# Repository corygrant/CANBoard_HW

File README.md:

# CANBoard_HW
CANBoard is a simple CAN enabled IO board, specifically designed to be used in devices like steering wheels/button boxes/panels/etc.

* 8 digital inputs
    * Ground switching
* 5 analog inputs
    * 5V max
* 4 digital outputs
    * Low side switch (open collector)
    * 0.5A max each
* STM32F303K8
* KiCad 7.0.0

# Goals
- Create a low cost device that my friends and I can use in our project cars
- Use components that are easily soldered by hand (hence 0805) and are preferably from my stock of frequently used parts (ex: LD1117S33CTR)
- Share my work with others for reference, inspiration or collaboration. 

If this project does help you in any way, I'd appreciate a message!

# [Store](https://dingo-electronics.square.site/product/canboard/3)

# Disclaimer
Please note that this product has been designed by a hobbyist, not a professional. It is intended for off-road and testing use only. Users should operate the product at their own discretion and risk. The designer explicitly disclaims any responsibility for damage or injury that may result from the use of this product.

# Schematic
[Schematic PDF](/Export/V2/CANBoard_HW_V2.pdf)

# DBC

DBC file can be found [here](https://github.com/corygrant/CANBoard_FW/tree/main/dbc)

# BOM

[Interactive BOM](https://htmlpreview.github.io/?https://github.com/corygrant/CANBoard_HW/blob/main/docs/bom/ibom.html)

# Jumpers
**CAN Term** : Soldering this jumper enables the 120 ohm terminating resistor across CANL/CANH

**CAN ID Jumpers 1 and 2** : Soldering these jumpers allows different base CAN IDs to be selected when using multiple CANBoards in the same bus
| 1      | 2      | Base CAN ID (Hex)|
| ------ | ------ | ----- |
| Open   | Open   | 0x640 |
| Closed | Open   | 0x650 |
| Open   | Closed | 0x660 |
| Closed | Closed | 0x670 |

# Firmware
[CANBoard firmware](https://github.com/corygrant/CANBoard_FW)

# Updating Firmware
Use [Tag Connect TC2030 cable](https://www.tag-connect.com/product/tc2030-ctx-nl-stdc14-for-use-with-stm32-processors-with-stlink-v3) 

# Images

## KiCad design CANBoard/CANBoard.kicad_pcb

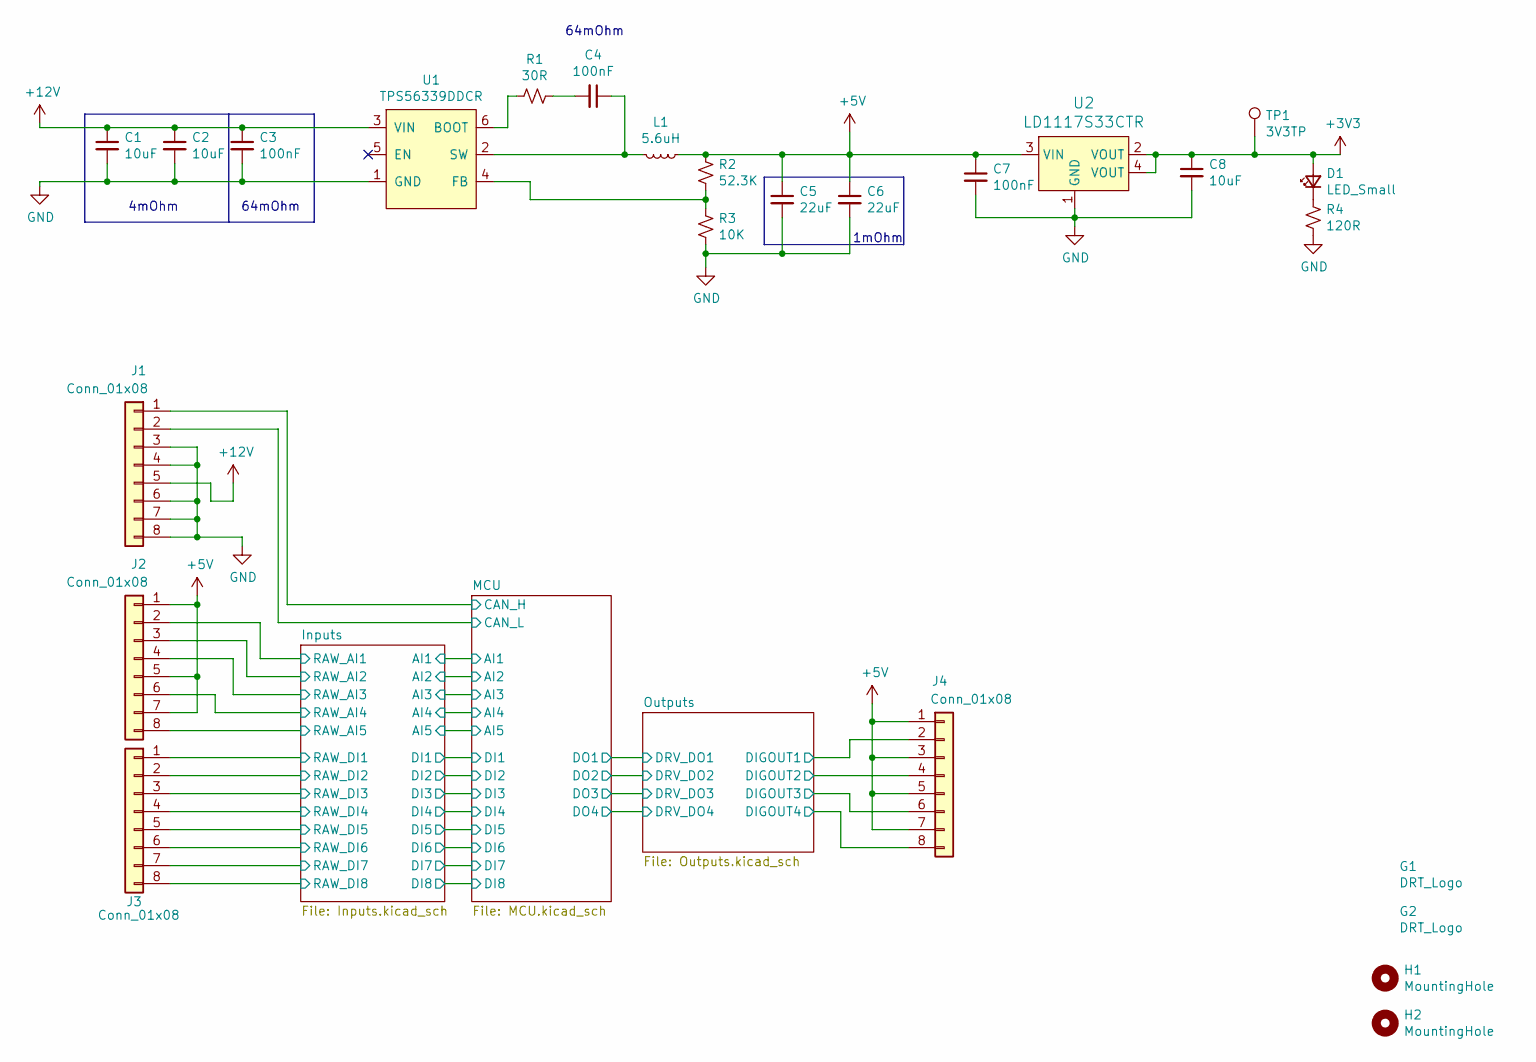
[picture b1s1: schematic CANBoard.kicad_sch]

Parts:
C1, C2, C8: 10uF; C_0805_2012Metric; Digi-Key_PN 490-10748-1-ND
C3, C4, C7: 100nF; C_0805_2012Metric; Digi-Key_PN 399-1169-1-ND
C5, C6: 22uF; C_0805_2012Metric; Digi-Key_PN 445-14560-1-ND
D1: LED_Small; LED_0805_2012Metric; Digi-Key_PN 475-2560-1-ND
G1: DRT_Logo; DRTLogo
G2: DRT_Logo; DingoFaceNoFill
H1, H2: MountingHole; MountingHole_3.2mm_M3_DIN965_Pad
J1, J2, J3, J4: Conn_01x08; PinHeader_1x08_P2.54mm_Vertical
L1: 5.6uH; Wuerth_LHMI; Digi-Key_PN 732-3339-1-ND
R1: 30R; R_0805_2012Metric; Digi-Key_PN RR12Q30DCT-ND
R2: 52.3K; R_0805_2012Metric; Digi-Key_PN P52.3KCCT-ND
R3: 10K; R_0805_2012Metric; Digi-Key_PN 311-10.0KCRDKR-ND
R4: 120R; R_0805_2012Metric; Digi-Key_PN 311-120CRCT-ND
TP1: 3V3TP; TestPoint_Pad_D1.0mm
U1: TPS56339DDCR; SOT-23-6_NoPin5; Digi-Key_PN 296-53568-1-ND
U2: LD1117S33CTR; SOT-223; MPN LD1117S33CTR; Digi-Key_PN 497-1241-1-ND

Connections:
+3V3: C8.1, D1.2 (A), TP1.1, U2.2 (VOUT), U2.4 (VOUT); also elsewhere on the board
+5V: C5.1, C6.1, C7.1, J2.1, J2.5, J2.7, J4.1, J4.3, J4.5, J4.7, L1.1, R2.2, U2.3 (VIN); also elsewhere on the board
+12V: C1.1, C2.1, C3.1, J1.5, U1.3 (VIN)
/Inputs/RAW_AI1: J2.2; also elsewhere on the board
/Inputs/RAW_AI2: J2.3; also elsewhere on the board
/Inputs/RAW_AI3: J2.4; also elsewhere on the board
/Inputs/RAW_AI4: J2.6; also elsewhere on the board
/Inputs/RAW_AI5: J2.8; also elsewhere on the board
/Inputs/RAW_DI1: J3.1; also elsewhere on the board
/Inputs/RAW_DI2: J3.2; also elsewhere on the board
/Inputs/RAW_DI3: J3.3; also elsewhere on the board
/Inputs/RAW_DI4: J3.4; also elsewhere on the board
/Inputs/RAW_DI5: J3.5; also elsewhere on the board
/Inputs/RAW_DI6: J3.6; also elsewhere on the board
/Inputs/RAW_DI7: J3.7; also elsewhere on the board
/Inputs/RAW_DI8: J3.8; also elsewhere on the board
/MCU/CAN_H: J1.1; also elsewhere on the board
/MCU/CAN_L: J1.2; also elsewhere on the board
/Outputs/DIGOUT1: J4.2; also elsewhere on the board
/Outputs/DIGOUT2: J4.4; also elsewhere on the board
/Outputs/DIGOUT3: J4.6; also elsewhere on the board
/Outputs/DIGOUT4: J4.8; also elsewhere on the board
GND: C1.2, C2.2, C3.2, C5.2, C6.2, C7.2, C8.2, J1.3, J1.4, J1.6, J1.7, J1.8, R3.1, R4.1, U1.1 (GND), U2.1 (GND); also elsewhere on the board
unnamed: C4.2, R1.1
unnamed: D1.1 (K), R4.2
unnamed: R1.2, U1.6 (BOOT)
unnamed: R2.1, R3.2, U1.4 (FB)
unnamed: C4.1, L1.2, U1.2 (SW)

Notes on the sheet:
1mOhm
4mOhm
64mOhm

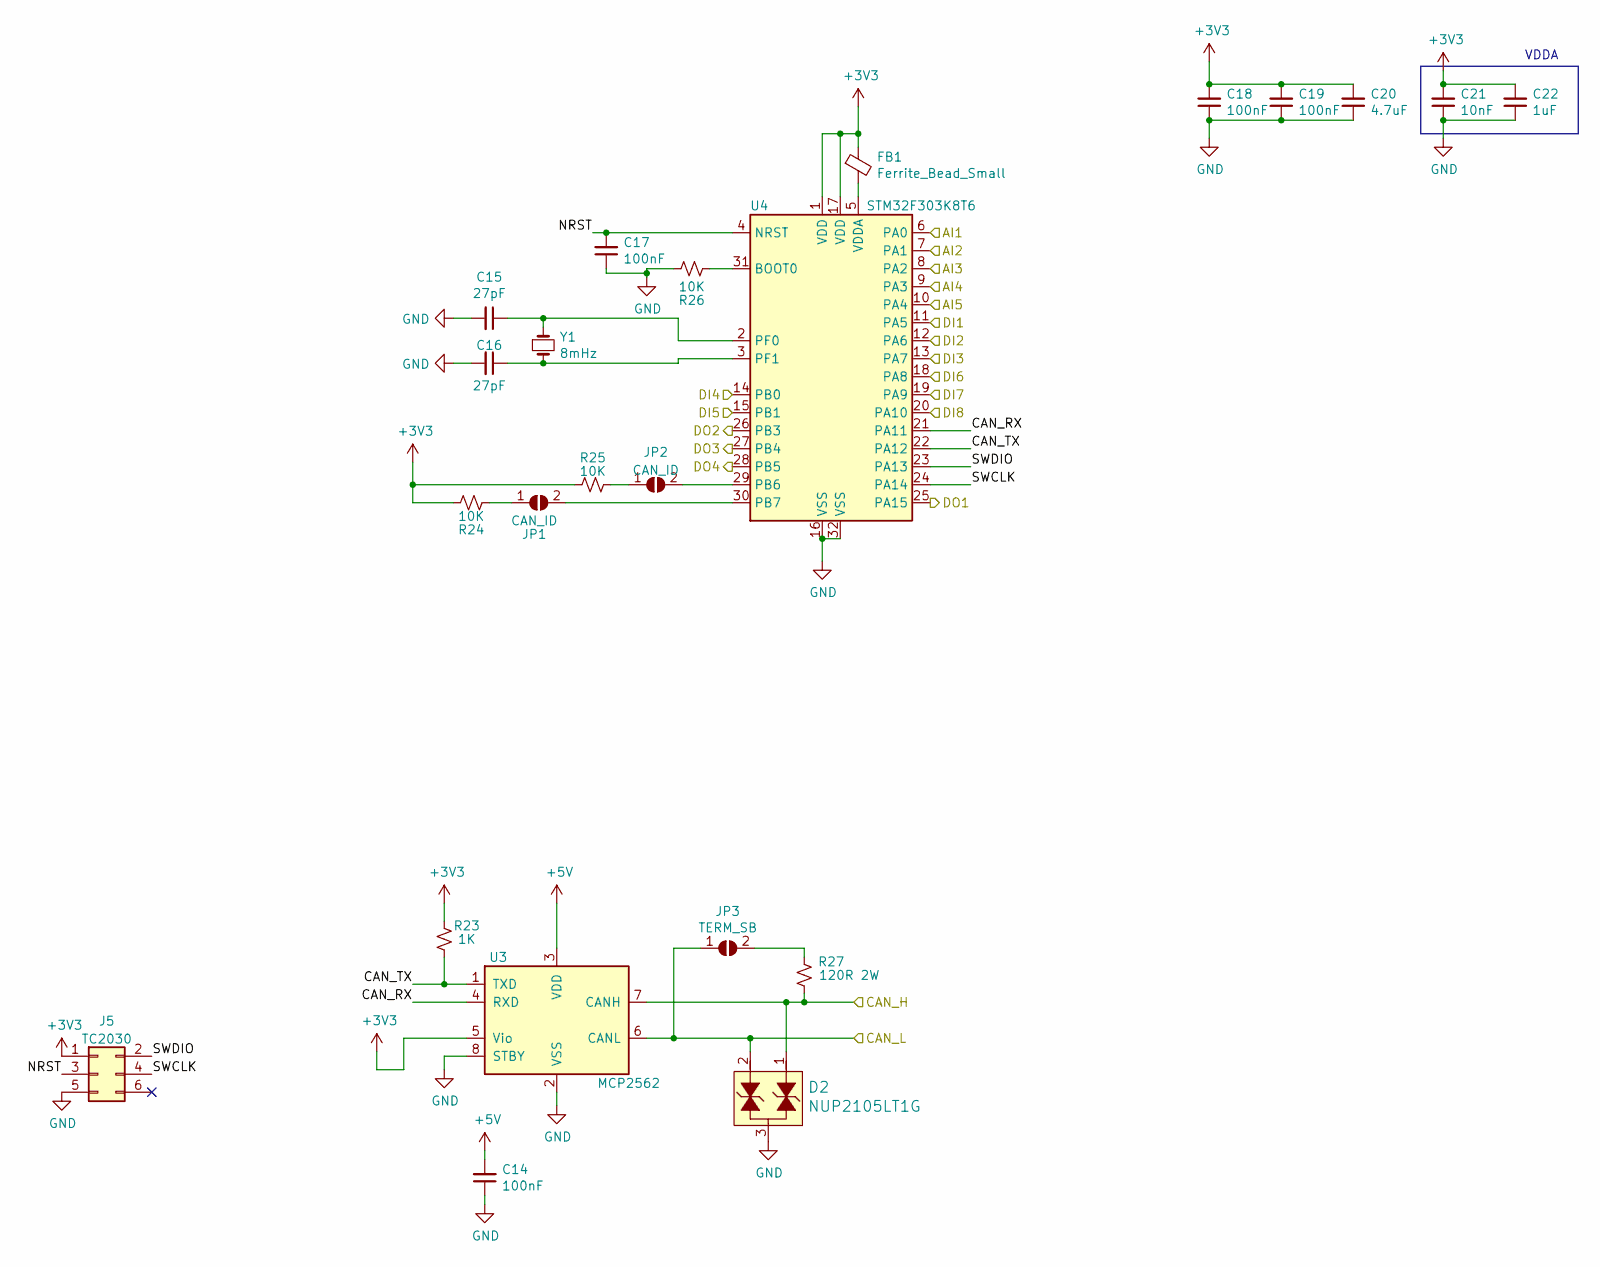
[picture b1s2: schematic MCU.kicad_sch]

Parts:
C14, C17, C18, C19: 100nF; C_0805_2012Metric; Digi-Key_PN 399-1169-1-ND
C15, C16: 27pF; C_0805_2012Metric; Digi-Key_PN 478-10518-1-ND
C20: 4.7uF; C_0805_2012Metric; Digi-Key_PN 1276-2873-1-ND
C21: 10nF; C_0805_2012Metric; Digi-Key_PN 311-1136-1-ND
C22: 1uF; C_0805_2012Metric; Digi-Key_PN 311-1365-1-ND
D2: NUP2105LT1G; SOT-23-3; MPN NUP2105LT1G; Digi-Key_PN NUP2105LT1GOSCT-ND
FB1: Ferrite_Bead_Small; R_0805_2012Metric; Digi-Key_PN 490-1054-1-ND
J5: TC2030; Tag-Connect_TC2030-IDC-NL_2x03_P1.27mm_Vertical
JP1, JP2: CAN_ID; SolderJumper-2_P1.3mm_Open_RoundedPad1.0x1.5mm
JP3: TERM_SB; SolderJumper-2_P1.3mm_Open_RoundedPad1.0x1.5mm
R23: 1K; R_0805_2012Metric; Digi-Key_PN 311-1.0KARCT-ND
R24, R25, R26: 10K; R_0805_2012Metric; Digi-Key_PN 311-10.0KCRDKR-ND
R27: 120R 2W; R_2512_6332Metric; Digi-Key_PN A116010CT-ND
U3: MCP2562; SOIC-8_3.9x4.9mm_P1.27mm; Digi-Key_PN MCP2562-H/SN-ND
U4: STM32F303K8T6; LQFP-32_7x7mm_P0.8mm; Digi-Key_PN 497-15828-ND
Y1: 8mHz; Crystal_SMD_5032-2Pin_5.0x3.2mm; Digi-Key_PN 535-10630-1-ND

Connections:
+3V3: C18.2, C19.2, C20.2, C21.2, C22.2, FB1.1, J5.1, R23.2, R24.2, R25.2, U3.5 (Vio), U4.1 (VDD), U4.17 (VDD); also elsewhere on the board
+5V: C14.2, U3.3 (VDD); also elsewhere on the board
/Inputs/AI1: U4.6 (PA0); also elsewhere on the board
/Inputs/AI2: U4.7 (PA1); also elsewhere on the board
/Inputs/AI3: U4.8 (PA2); also elsewhere on the board
/Inputs/AI4: U4.9 (PA3); also elsewhere on the board
/Inputs/AI5: U4.10 (PA4); also elsewhere on the board
/Inputs/DI1: U4.11 (PA5); also elsewhere on the board
/Inputs/DI2: U4.12 (PA6); also elsewhere on the board
/Inputs/DI3: U4.13 (PA7); also elsewhere on the board
/Inputs/DI4: U4.14 (PB0); also elsewhere on the board
/Inputs/DI5: U4.15 (PB1); also elsewhere on the board
/Inputs/DI6: U4.18 (PA8); also elsewhere on the board
/Inputs/DI7: U4.19 (PA9); also elsewhere on the board
/Inputs/DI8: U4.20 (PA10); also elsewhere on the board
/MCU/CAN_H: D2.1, R27.1, U3.7 (CANH); also elsewhere on the board
/MCU/CAN_L: D2.2, JP3.1 (A), U3.6 (CANL); also elsewhere on the board
/MCU/CAN_RX: U3.4 (RXD), U4.21 (PA11)
/MCU/CAN_TX: R23.1, U3.1 (TXD), U4.22 (PA12)
/MCU/DO1: U4.25 (PA15); also elsewhere on the board
/MCU/DO2: U4.26 (PB3); also elsewhere on the board
/MCU/DO3: U4.27 (PB4); also elsewhere on the board
/MCU/DO4: U4.28 (PB5); also elsewhere on the board
/MCU/NRST: C17.2, J5.3, U4.4 (NRST)
/MCU/SWCLK: J5.4, U4.24 (PA14)
/MCU/SWDIO: J5.2, U4.23 (PA13)
GND: C14.1, C15.2, C16.2, C17.1, C18.1, C19.1, C20.1, C21.1, C22.1, D2.3, J5.5, R26.2, U3.2 (VSS), U3.8 (STBY), U4.16 (VSS), U4.32 (VSS); also elsewhere on the board
unnamed: JP1.1 (A), R24.1
unnamed: JP1.2 (B), U4.30 (PB7)
unnamed: JP2.1 (A), R25.1
unnamed: JP2.2 (B), U4.29 (PB6)
unnamed: JP3.2 (B), R27.2
unnamed: R26.1, U4.31 (BOOT0)
unnamed: C15.1, U4.2 (PF0), Y1.1
unnamed: C16.1, U4.3 (PF1), Y1.2
unnamed: FB1.2, U4.5 (VDDA)

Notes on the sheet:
VDDA

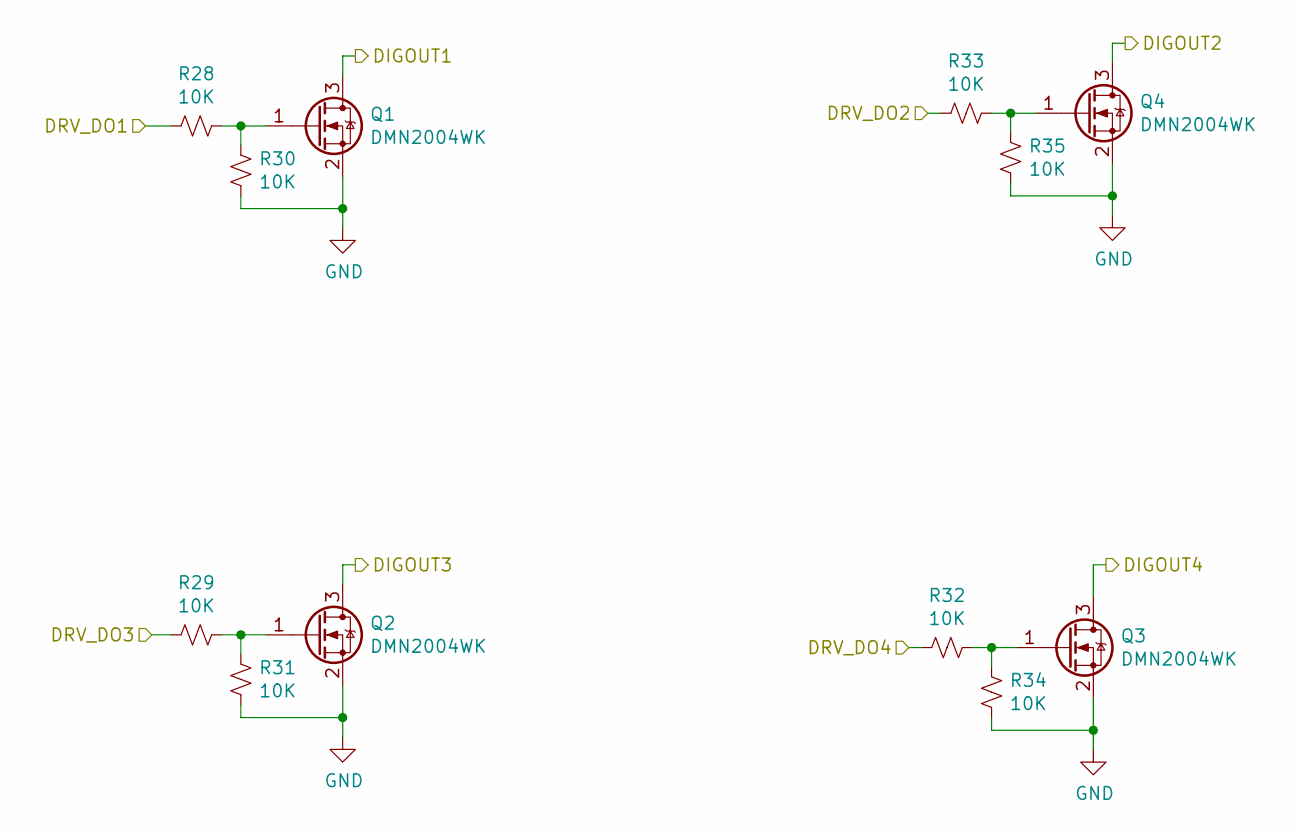
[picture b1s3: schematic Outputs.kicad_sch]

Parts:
Q1, Q2, Q3, Q4: DMN2004WK; SOT-323_SC-70; Digi-Key_PN DMN2004WKDICT-ND
R28, R29, R30, R31, R32, R33, R34, R35: 10K; R_0805_2012Metric; Digi-Key_PN 311-10.0KCRDKR-ND

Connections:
/MCU/DO1: R28.2; also elsewhere on the board
/MCU/DO2: R33.2; also elsewhere on the board
/MCU/DO3: R29.2; also elsewhere on the board
/MCU/DO4: R32.2; also elsewhere on the board
/Outputs/DIGOUT1: Q1.3 (D); also elsewhere on the board
/Outputs/DIGOUT2: Q4.3 (D); also elsewhere on the board
/Outputs/DIGOUT3: Q2.3 (D); also elsewhere on the board
/Outputs/DIGOUT4: Q3.3 (D); also elsewhere on the board
GND: Q1.2 (S), Q2.2 (S), Q3.2 (S), Q4.2 (S), R30.1, R31.1, R34.1, R35.1; also elsewhere on the board
unnamed: Q1.1 (G), R28.1, R30.2
unnamed: Q2.1 (G), R29.1, R31.2
unnamed: Q3.1 (G), R32.1, R34.2
unnamed: Q4.1 (G), R33.1, R35.2

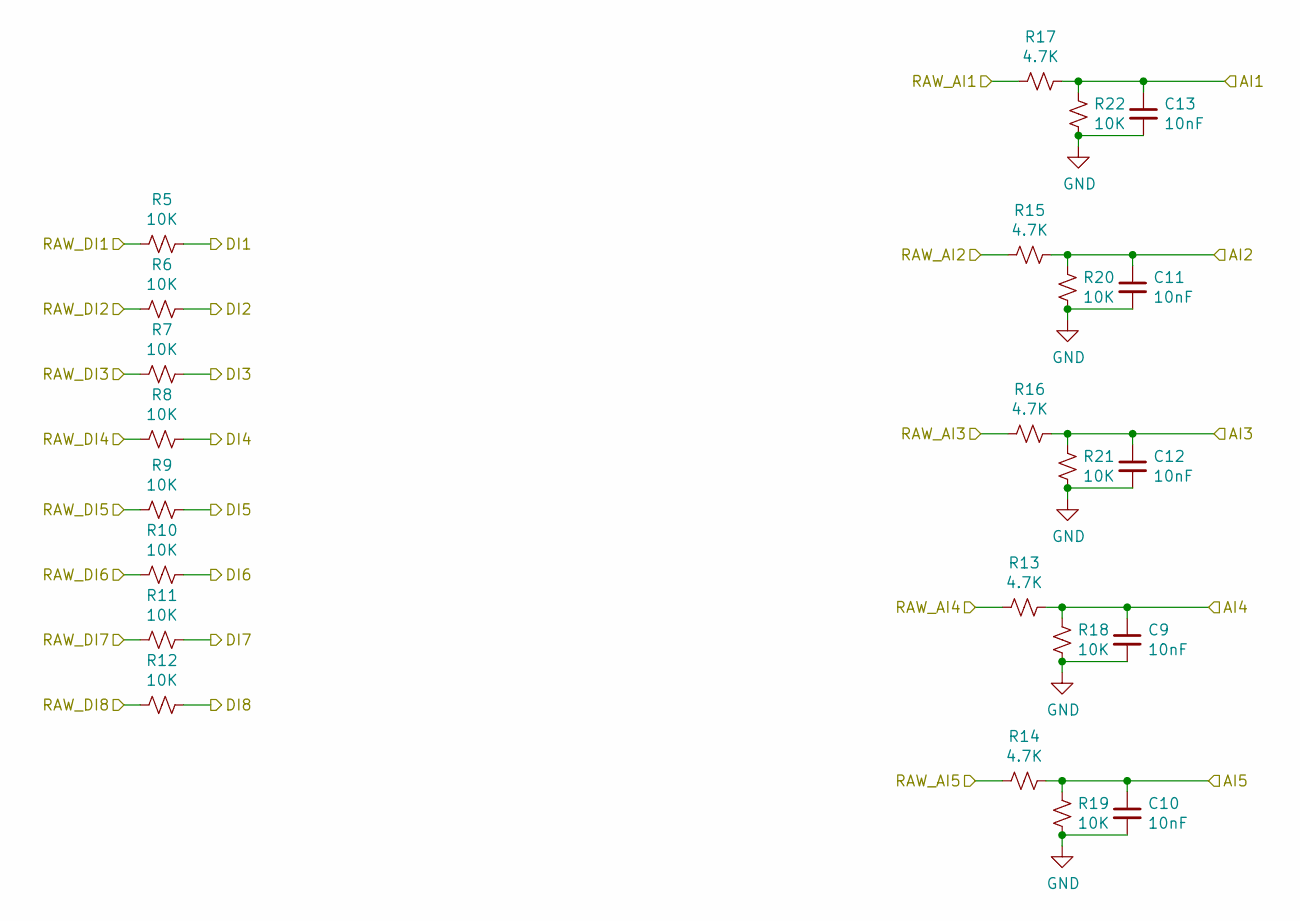
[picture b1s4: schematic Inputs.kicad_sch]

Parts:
C9, C10, C11, C12, C13: 10nF; C_0805_2012Metric; Digi-Key_PN 311-1136-1-ND
R5, R6, R7, R8, R9, R10, R11, R12, R18, R19, R20, R21, R22: 10K; R_0805_2012Metric; Digi-Key_PN 311-10.0KCRDKR-ND
R13, R14, R15, R16, R17: 4.7K; R_0805_2012Metric; Digi-Key_PN 311-4.70KCRCT-ND

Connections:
/Inputs/AI1: C13.1, R17.1, R22.2; also elsewhere on the board
/Inputs/AI2: C11.1, R15.1, R20.2; also elsewhere on the board
/Inputs/AI3: C12.1, R16.1, R21.2; also elsewhere on the board
/Inputs/AI4: C9.1, R13.1, R18.2; also elsewhere on the board
/Inputs/AI5: C10.1, R14.1, R19.2; also elsewhere on the board
/Inputs/DI1: R5.1; also elsewhere on the board
/Inputs/DI2: R6.1; also elsewhere on the board
/Inputs/DI3: R7.1; also elsewhere on the board
/Inputs/DI4: R8.1; also elsewhere on the board
/Inputs/DI5: R9.1; also elsewhere on the board
/Inputs/DI6: R10.1; also elsewhere on the board
/Inputs/DI7: R11.1; also elsewhere on the board
/Inputs/DI8: R12.1; also elsewhere on the board
/Inputs/RAW_AI1: R17.2; also elsewhere on the board
/Inputs/RAW_AI2: R15.2; also elsewhere on the board
/Inputs/RAW_AI3: R16.2; also elsewhere on the board
/Inputs/RAW_AI4: R13.2; also elsewhere on the board
/Inputs/RAW_AI5: R14.2; also elsewhere on the board
/Inputs/RAW_DI1: R5.2; also elsewhere on the board
/Inputs/RAW_DI2: R6.2; also elsewhere on the board
/Inputs/RAW_DI3: R7.2; also elsewhere on the board
/Inputs/RAW_DI4: R8.2; also elsewhere on the board
/Inputs/RAW_DI5: R9.2; also elsewhere on the board
/Inputs/RAW_DI6: R10.2; also elsewhere on the board
/Inputs/RAW_DI7: R11.2; also elsewhere on the board
/Inputs/RAW_DI8: R12.2; also elsewhere on the board
GND: C9.2, C10.2, C11.2, C12.2, C13.2, R18.1, R19.1, R20.1, R21.1, R22.1; also elsewhere on the board

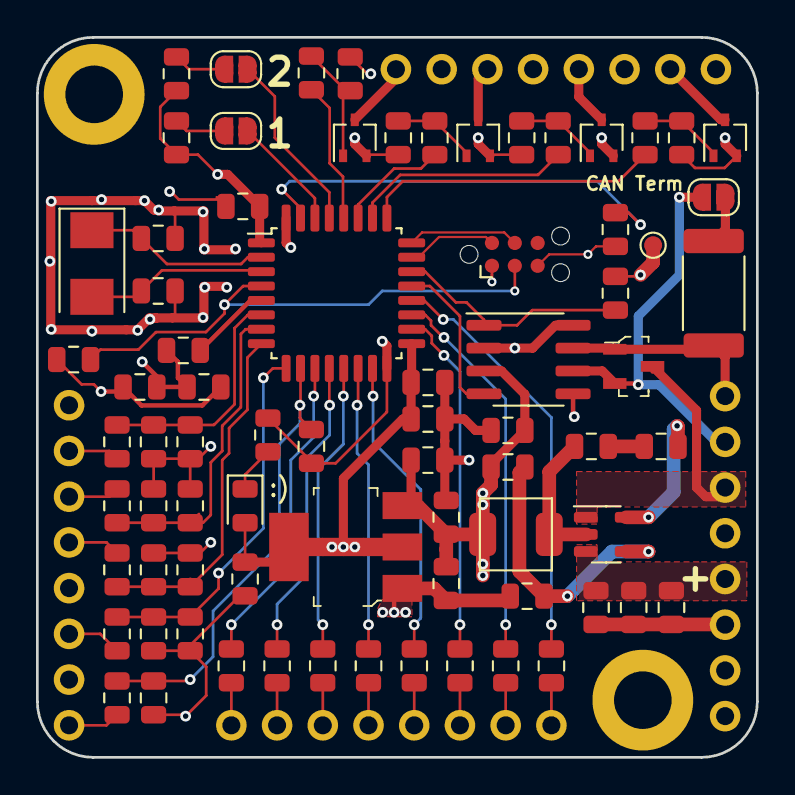
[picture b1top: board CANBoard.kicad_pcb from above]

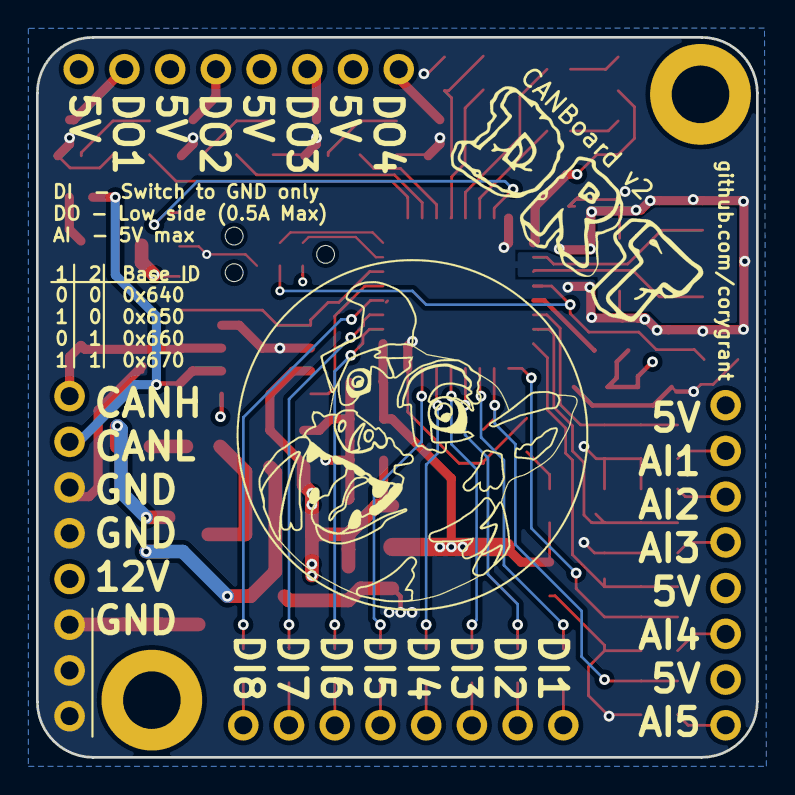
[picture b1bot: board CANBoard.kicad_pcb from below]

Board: 4 copper layers, 40.0 x 40.0 mm, 83 parts (2 on the bottom side), 63 nets.

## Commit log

2021-04-10 Reorganizing files
2021-05-12 Swapped MCP2551 to MCP2562
2022-10-15 Kicad V6 updates
2022-12-13 Convert to kicad v6
2023-01-05 Updated gitignore
2023-01-05 Removed files from the index (now ignored)
2023-02-18 V2 updates
    Removed FRAM, I2C and SWD pins. Added ID solder jumpers and Tag Connect
2023-02-19 Updated outputs, added JLCPCB LCSC part nums
2023-02-19 Updated images to V2
2023-02-19 Render missing component model
2023-02-19 Updated gitignore to remove autosave file
2023-02-19 initial programming
2023-02-19 hopefully better placement for v1 gerbers?
2023-02-19 same gerbers are already present in CANBoard_HW_V2_gerbers.zip and I got confused already
2023-02-19 i see kicad 6
2023-02-19 second set of same exact individual files?
2023-02-19 Oops had .csv in the gitignore #5
2023-02-20 Updated to Kicad 7, updated readme
    Changed Renders directory to Images
2023-02-20 Update README.md
    Added jumper info
2023-02-21 Fixed JLCPCB file issues
    I had L1 set as THT, which left it out of the export. I also had the BOM grouped which didn't work with their import tool. #9
2023-02-21 Added documentation describing JLCPCB process #8
2023-03-05 Updated base IDs
2023-03-06 #12 Removed U1 EN pin 5, updated documentation
2023-08-24 Update PartPlacement.jpg
    Power LED was backwards
2024-04-03 Updated JLC inductor part number
2024-05-01 Updated images
2024-07-02 Added step model
2024-07-13 ignore
2024-07-13 update gitignore
2024-09-06 Updated to Kicad 8
2024-12-31 add dimensions drawing
2025-03-25 dbc and dbc builder added
2025-04-23 gha build dbc
2025-04-23 move workflow
2025-04-23 permission denied error
2025-04-23 set permissions
2025-04-23 copied file, oops
2025-04-23 add msg3
2025-04-23 add to build_db
2025-04-24 only run generate dbc on dbc_builder change
2025-04-24 dbc change test
2025-04-24 move dbc to fw repo
2025-04-24 add dbc file link
2025-08-19 move footprints to project library
2025-12-11 add ibom
2025-12-11 Fix link to Interactive BOM in README.md
